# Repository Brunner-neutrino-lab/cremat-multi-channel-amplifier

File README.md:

# Multi-channel Cremat amplifier

A **12-channel** SiPM charge-sensitive preamplifier + Gaussian shaper board, derived
from the Brunner-lab **6-channel Cremat CSP & Shaper board**
([`cremat-x6-board`](reference/cremat-x6-board/)) with four deliberate changes:

1. **12 channels** (was 6).
2. **0805 passives wherever possible** (was a mix of larger imperial sizes).
3. **A Cremat CR-210 baseline restorer on every channel**, *optional* — populate the
   module **or** an 0805 `0R` jumper to bypass it.
4. **An on-board SiPM bias front-end on every channel**: a `BIAS_IN` feed through an
   *optional* RC-in-series-with-R **bias filter**, then a node shared by the **SiPM**
   (DC-coupled) and the **amplifier** (AC-coupled). The detector and the amplifier hang
   off the same biased node.

> This repository is the **design specification + build documentation** for the new
> board. It is structured to mirror the Brunner-lab **`ets-breakout`** project, which is
> included as the *reference for how to document and build*. The KiCad implementation is
> the next track (see [Status](#status)).

## What each channel does (new signal chain)

```
                          bias filter (optional, 0R-bypassable)
 BIAS_IN ───►  Rf1 ──┬── Rf2 ──►──┐
                     │            │   FRONT-END NODE
                    Cf            ├─────────────► SIPM   (DC-coupled: reverse-biases the detector)
                     │            │
                    GND           └─► Cc ─► CR-11X ─► CR-200-X ─► [CR-210] ─► buffer ─► OUTPUT
                                     (AC)   CSP        shaper     BLR(opt)   THS3491    (50 Ω
                                                       +P/Z trim  0R-byp.    DNP-def     coax)
```

- **`BIAS_IN` → bias filter → front-end node.** "RC in series with R": series `Rf1`,
  shunt `Cf` to ground, series `Rf2`. The whole filter is bypassable with 0R jumpers.
- **Front-end node → `SIPM` (DC-coupled).** The filtered bias voltage reverse-biases the
  detector directly.
- **Front-end node → `Cc` → amplifier (AC-coupled).** Only the SiPM's fast current pulse
  reaches the charge-sensitive preamp; the DC bias is blocked by `Cc`.
- **CR-11X → CR-200-X → CR-210 → buffer → output**, the classic Cremat chain. The CR-210
  baseline restorer is new and optional.

Full detail: [docs/hardware/channel.md](docs/hardware/channel.md).

## Documentation map

> **Looking for the actual orderable board? It is [`final-board/twelve-channel/`](final-board/twelve-channel/).**
> Reviewing it → [REVIEW.md](final-board/twelve-channel/REVIEW.md) · ordering it →
> [ORDERING.md](final-board/twelve-channel/ORDERING.md) · resuming work on it →
> [HANDOFF.md](final-board/twelve-channel/HANDOFF.md).

| Doc | Contents |
|-----|----------|
| **[final-board/twelve-channel/REVIEW.md](final-board/twelve-channel/REVIEW.md)** | **Design-review pack** — verified state, the acceptance gate, and what needs human eyes before ordering |
| [final-board/twelve-channel/INTERFACE.md](final-board/twelve-channel/INTERFACE.md) | The final board: layout intent, connector map, stackup, per-channel cell |
| [final-board/twelve-channel/ORDERING.md](final-board/twelve-channel/ORDERING.md) | Buy sheet — JLCPCB (fab + SMT) + DigiKey (hand parts), quantities, upload steps |
| [final-board/twelve-channel/HANDOFF.md](final-board/twelve-channel/HANDOFF.md) | Resume on a new machine: toolchain, paths, regeneration commands, gotchas |
| [docs/agent-project/](docs/agent-project/) | **Parallel agent-developed build** — bottom-up (per-chip eval boards → single channel → 12-ch board), 12 tracks with briefs, conventions, session-log/report protocol. **Start at [docs/agent-project/README.md](docs/agent-project/README.md).** *(Historical: intermediate figures here — e.g. bias ≤ 60 V, board 235.1 × 264.1 mm — are superseded by the final board.)* |
| [docs/development-plan.md](docs/development-plan.md) | Earlier work-track breakdown (the rapid top-down build in `hardware/`); superseded by the agent-project for the final design |
| [docs/architecture.md](docs/architecture.md) | System/board block diagram, channel signal chain, design partitioning |
| [docs/modifications.md](docs/modifications.md) | **The four changes vs. `cremat-x6-board`, with rationale + the optional/DNP jumper scheme** |
| [docs/hardware/channel.md](docs/hardware/channel.md) | Per-channel circuit: bias front-end, AC/DC coupling, CSP/shaper/BLR/buffer, jumpers |
| [docs/hardware/circuit-design.md](docs/hardware/circuit-design.md) | **Front-end values for the Hamamatsu VUV4** — bias filter, coupling, polarity, CR-112 gain/range |
| [docs/hardware/board.md](docs/hardware/board.md) | 12-channel board: power distribution, connectors, layout intent |
| [docs/hardware/bom.md](docs/hardware/bom.md) | 0805 strategy, Cremat modules, optional-population (DNP) variants |
| [docs/hardware/pcb-design-rules.md](docs/hardware/pcb-design-rules.md) | Net classes, trace widths, HV creepage, guard rings |
| [docs/hardware/component-libraries.md](docs/hardware/component-libraries.md) | Symbols + footprints to provide (Cremat SIP-8, 0805 passives, jumpers) |
| [docs/fabrication/fabrication-guide.md](docs/fabrication/fabrication-guide.md) | Fab output generation, assembly, population variants |
| [docs/operation/user-guide.md](docs/operation/user-guide.md) | Power-up, biasing SiPMs, choosing populate/bypass options |
| [docs/session-report.md](docs/session-report.md) | Integration/manager handoff: tracks, decisions, what's done vs. open |

## References (git submodules)

| Path | Repo | Role |
|------|------|------|
| [reference/cremat-x6-board/](reference/cremat-x6-board/) | `Brunner-neutrino-lab/cremat-x6-board` | **What we're building** — the 6-channel CR-110/CR-200 eval board this design derives from |
| [reference/ets-breakout/](reference/ets-breakout/) | `Brunner-neutrino-lab/ets-breakout` | **How we build/document** — KiCad-from-source-of-truth pipeline + doc structure to imitate |
| [reference/cremat-CR-160-R7/](reference/cremat-CR-160-R7/) | `CrematInc/CR-160-R7` | **CR-210 pinout + integration** — Cremat's open-source CR-200/CR-210 eval board (the CR-210 bypass-jumper scheme) |
| [reference/cremat-CR-150-R5/](reference/cremat-CR-150-R5/) | `CrematInc/CR-150-R5` | **CR-11X reference** — Cremat's open-source CSP eval board (source of the CR-11X symbol) |

Clone with submodules:

```
git clone --recurse-submodules <this-repo>
# or, in an existing clone:
git submodule update --init --recursive
```

## Status

- **Specification + documentation: complete.** This repo fully specifies the modified
  12-channel board.
- **Development is divided into tracks** — see [docs/development-plan.md](docs/development-plan.md).
  **Phase 1 is built:** [hardware/](hardware/) has the `kicad-cli`-validated symbol library
  ([hardware/lib/cremat.kicad_sym](hardware/lib/cremat.kicad_sym)), the project + net classes,
  lib tables, the fielded BOM ([hardware/bom/](hardware/bom/)), the golden per-channel netlist
  ([hardware/integration-notes.md](hardware/integration-notes.md)), and the mechanical spec
  ([hardware/mechanical.md](hardware/mechanical.md)). **Track 5 (schematic) is done** — the
  12-channel hierarchical schematic is generated by [hardware/gen_sch.py](hardware/gen_sch.py)
  and is **ERC-clean (0 errors)** with a netlist that matches the spec node-by-node. **Layout
  + fab (Tracks 6–7)** remain — guide: [hardware/BUILD-IN-KICAD.md](hardware/BUILD-IN-KICAD.md).
- **CR-210 pinout + bypass-jumper integration: confirmed** against Cremat's open-source
  [CR-160-R7](reference/cremat-CR-160-R7/) board (pin 2 = GND vs the CR-200's P/Z).
- **Build decisions resolved** (D1–D6, see the plan): bias ≤ 70 V (100 V parts); all
  per-channel I/O is **MCX `CONMCX013`** (`BIAS_IN`, `SIPM`, `TEST`, `OUT_50` — **`BIAS_IN` is
  per-channel**, 4/channel → 48 MCX/board); modules **CR-112** + **CR-200-1µs** (+ CR-210),
  **socketed** on Samtec SS-108-TT-2 SIP-8 sockets (36/board), the modules plug in; rack-mounted,
  **one board per 1U Hammond RM1U1908VBK case, boards daisy-chained**; first build = Full.
- **Front-end designed for the Hamamatsu VUV4** (S13370, 45–55 V, ≈220 fC/V, Cdet≈1.28 nF):
  bias filter `Rf1=Rf2=10 kΩ`, `Cf=100 nF`, `Cc=0.22 µF`; cathode-on-node +45–55 V; CR-112
  ([docs/hardware/circuit-design.md](docs/hardware/circuit-design.md)).
- **Enclosure (D5):** **Hammond RM1U1908VBK** (1U, vented), **one board per case**; boards are
  **daisy-chained** (each board in its own 1U box, `J_DAISY` passes the raw rails box-to-box).
  Board outline **213.2 × 334.7 mm**; it mounts on standoffs off the bottom cover and passes
  **through a ~340 × 7 mm milled slot** in each front/rear panel (slot-through, protruding ~5 mm;
  the MCX faces sit ~8.6 mm proud). Usable interior height 40.09 mm; tall parts must clear it.
  Inputs (`BIAS_IN`+`SIPM`) on one long edge, outputs (`OUT_50`) on the other (24 MCX per long edge).
- **Open items**: final jack/outline placement (Track 4), and bench-verify (CR-112 output
  sign, warm/cold OV offset, single-p.e. range, P/Z trim). Power terminals are resolved —
  two 3-pos 5.08 mm Phoenix screw terminals, `J_PWR` (supply in) + `J_DAISY` (raw rails out).

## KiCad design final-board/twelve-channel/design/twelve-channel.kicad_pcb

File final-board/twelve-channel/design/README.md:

# twelve-channel — design (schematic + PCB)

12-channel SiPM CSP + shaper + BLR + buffer board, built from the reworked single channel
(`../../../integration/single-channel/design/`) as the single source of truth.

- **Schematic** = KiCad **hierarchical**: the single channel (minus board power entry)
  instantiated 12× as `channel.kicad_sch`, plus a root `twelve-channel.kicad_sch` with the 12
  sheet instances + one common power section (power in + board-to-board daisy + up-rated
  reverse-polarity/PTC block + 470 µF bulk). Per-channel nets auto-scope to `/chNN/<net>`.
- **PCB** = **tile-and-replicate**: the routed single-channel channel row is cloned 12× (offset
  25 mm in Y, refs re-mapped via role, nets re-mapped `/X`→`/chNN/X`); board-wide plane pours
  carry the rails so the router does no per-channel work; only the common section is routed.

## Pipeline (run in order; KiCad 10 bundled Python)

```
PY="C:/Program Files/KiCad/10.0/bin/python.exe"
CLI="C:/Program Files/KiCad/10.0/bin/kicad-cli.exe"

# --- schematic ---
"$PY" gen_sch.py                       # -> channel.kicad_sch, twelve-channel.kicad_sch, .kicad_pro
"$CLI" sch erc twelve-channel.kicad_sch
"$CLI" sch export netlist --format kicadsexpr -o twelve-channel.net twelve-channel.kicad_sch

# --- PCB (needs twelve-channel.net from the step above) ---
"$PY" gen_pcb.py                       # tile x12 + common section + planes + outline (+ .kicad_dru)
"$PY" fill_zones.py                    # fill the 4 plane zones (separate pass; in-memory fill segfaults)
"$PY" polish_silk.py                   # move dense refdes/fields F.Silkscreen -> F.Fab
"$CLI" pcb drc --schematic-parity twelve-channel.kicad_pcb    # gate: 0 / 0 / 0
```

Note: `gen_pcb.py` resets silk and adds visible common-part fields, so **`polish_silk.py` must
run after every `gen_pcb.py`**. The `twelve-channel.net` netlist is the authoritative source
for the PCB's per-pad nets, footprint values, and BOM fields (regenerate it after any schematic
change before re-running `gen_pcb.py`).

## Result

213.2 × 334.7 mm, 4-layer (widened 138 → 180 → 213.2 mm to span the Hammond RM1U1908VBK 1U case —
one board per case, slot-through the front/rear panels; the output/bias MCX row was shifted to the
far edge with F.Cu trace extensions). 468 footprints (464 refdes'd parts + 4 M3), 4 plane
zones. (The BOM lists 500 line-item parts = the 464 placed + the 36 SIP-8 sockets, which
share the module sites' PinSocket_1x08 footprints.)
**DRC 0 violations / 0 unconnected / 0 schematic-parity.** Render: `twelve-channel-3d.png`.

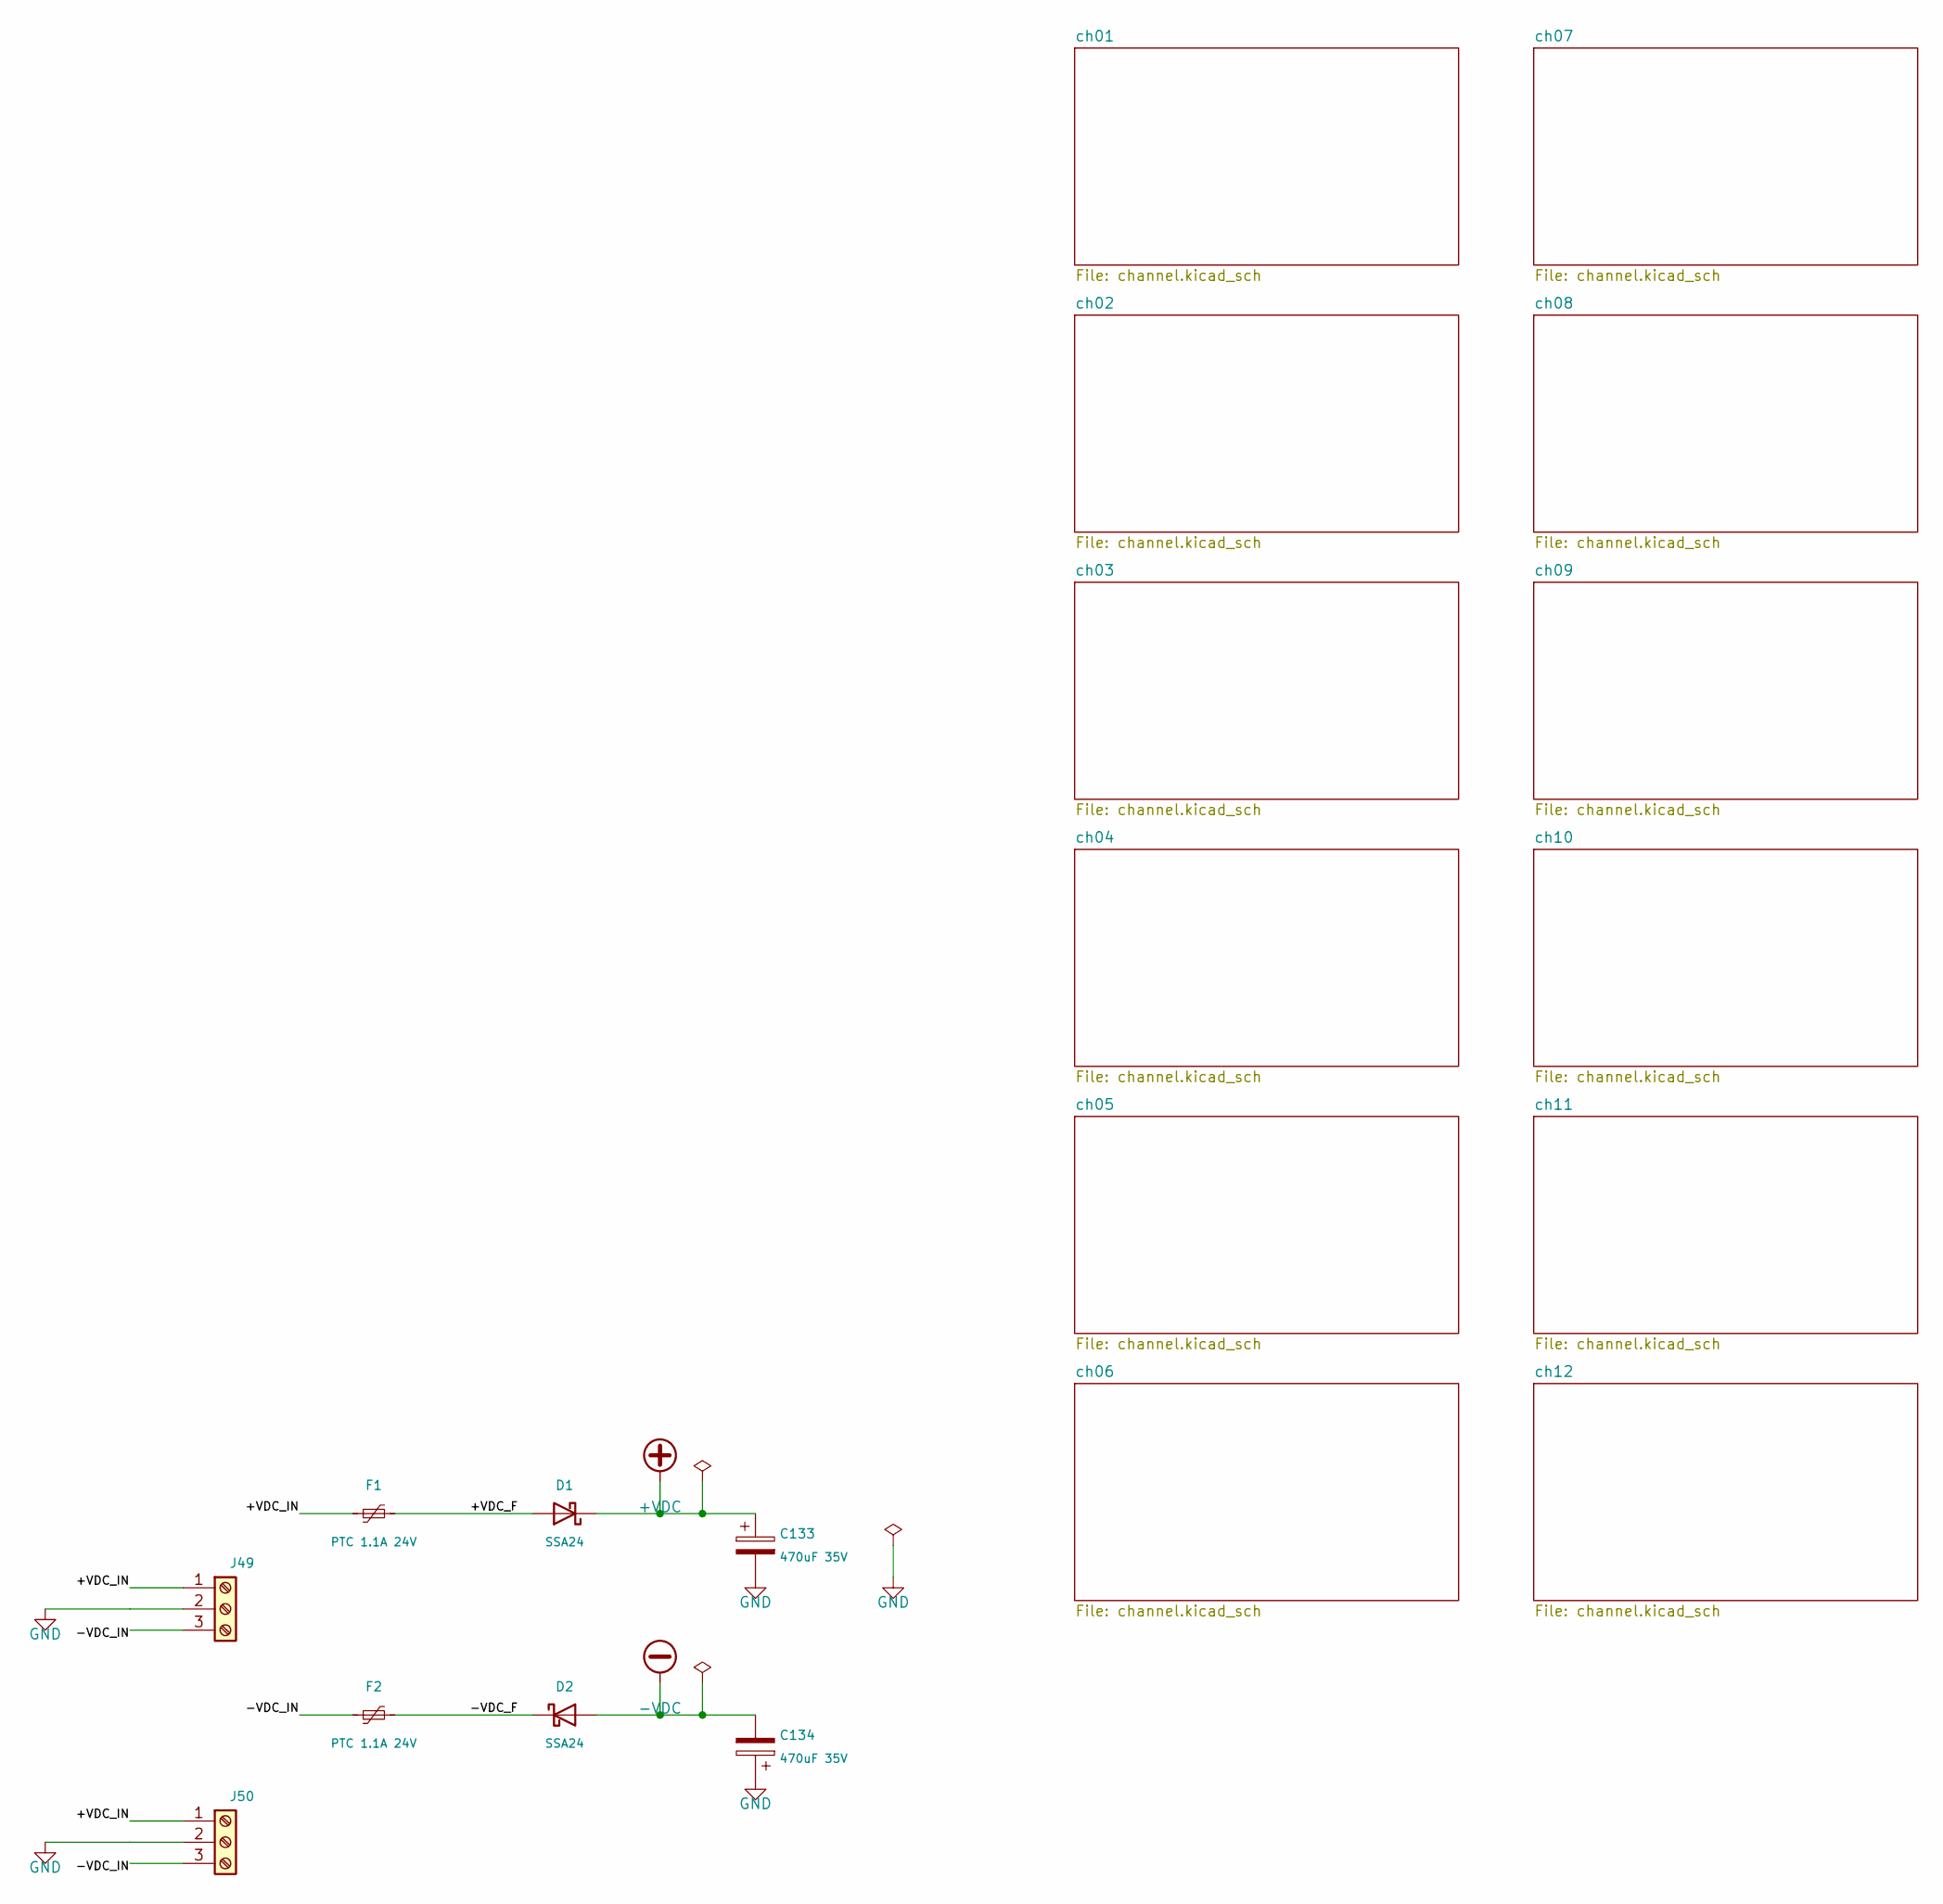
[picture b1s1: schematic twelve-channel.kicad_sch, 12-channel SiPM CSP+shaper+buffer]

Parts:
C133, C134: 470uF 35V; CP_Elec_10x10.5; MPN EEE-FN1V471UP
D1, D2: SSA24; D_SMA; MPN SSA24
F1, F2: PTC 1.1A 24V; Fuse_1812_4532Metric; MPN 1812L110/24DR
J49, J50: Screw terminal 3-pos 5.08mm; TerminalBlock_Phoenix_MKDS-1,5-3_1x03_P5.00mm_Horizontal; MPN 1715734

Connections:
+VDC: C133.1, D1.1 (K); also elsewhere on the board
-VDC: C134.2, D2.2 (A); also elsewhere on the board
/+VDC_F: D1.2 (A), F1.2
/+VDC_IN: F1.1, J49.1, J50.1
/-VDC_F: D2.1 (K), F2.2
/-VDC_IN: F2.1, J49.3, J50.3
GND: C133.2, C134.1, J49.2, J50.2; also elsewhere on the board

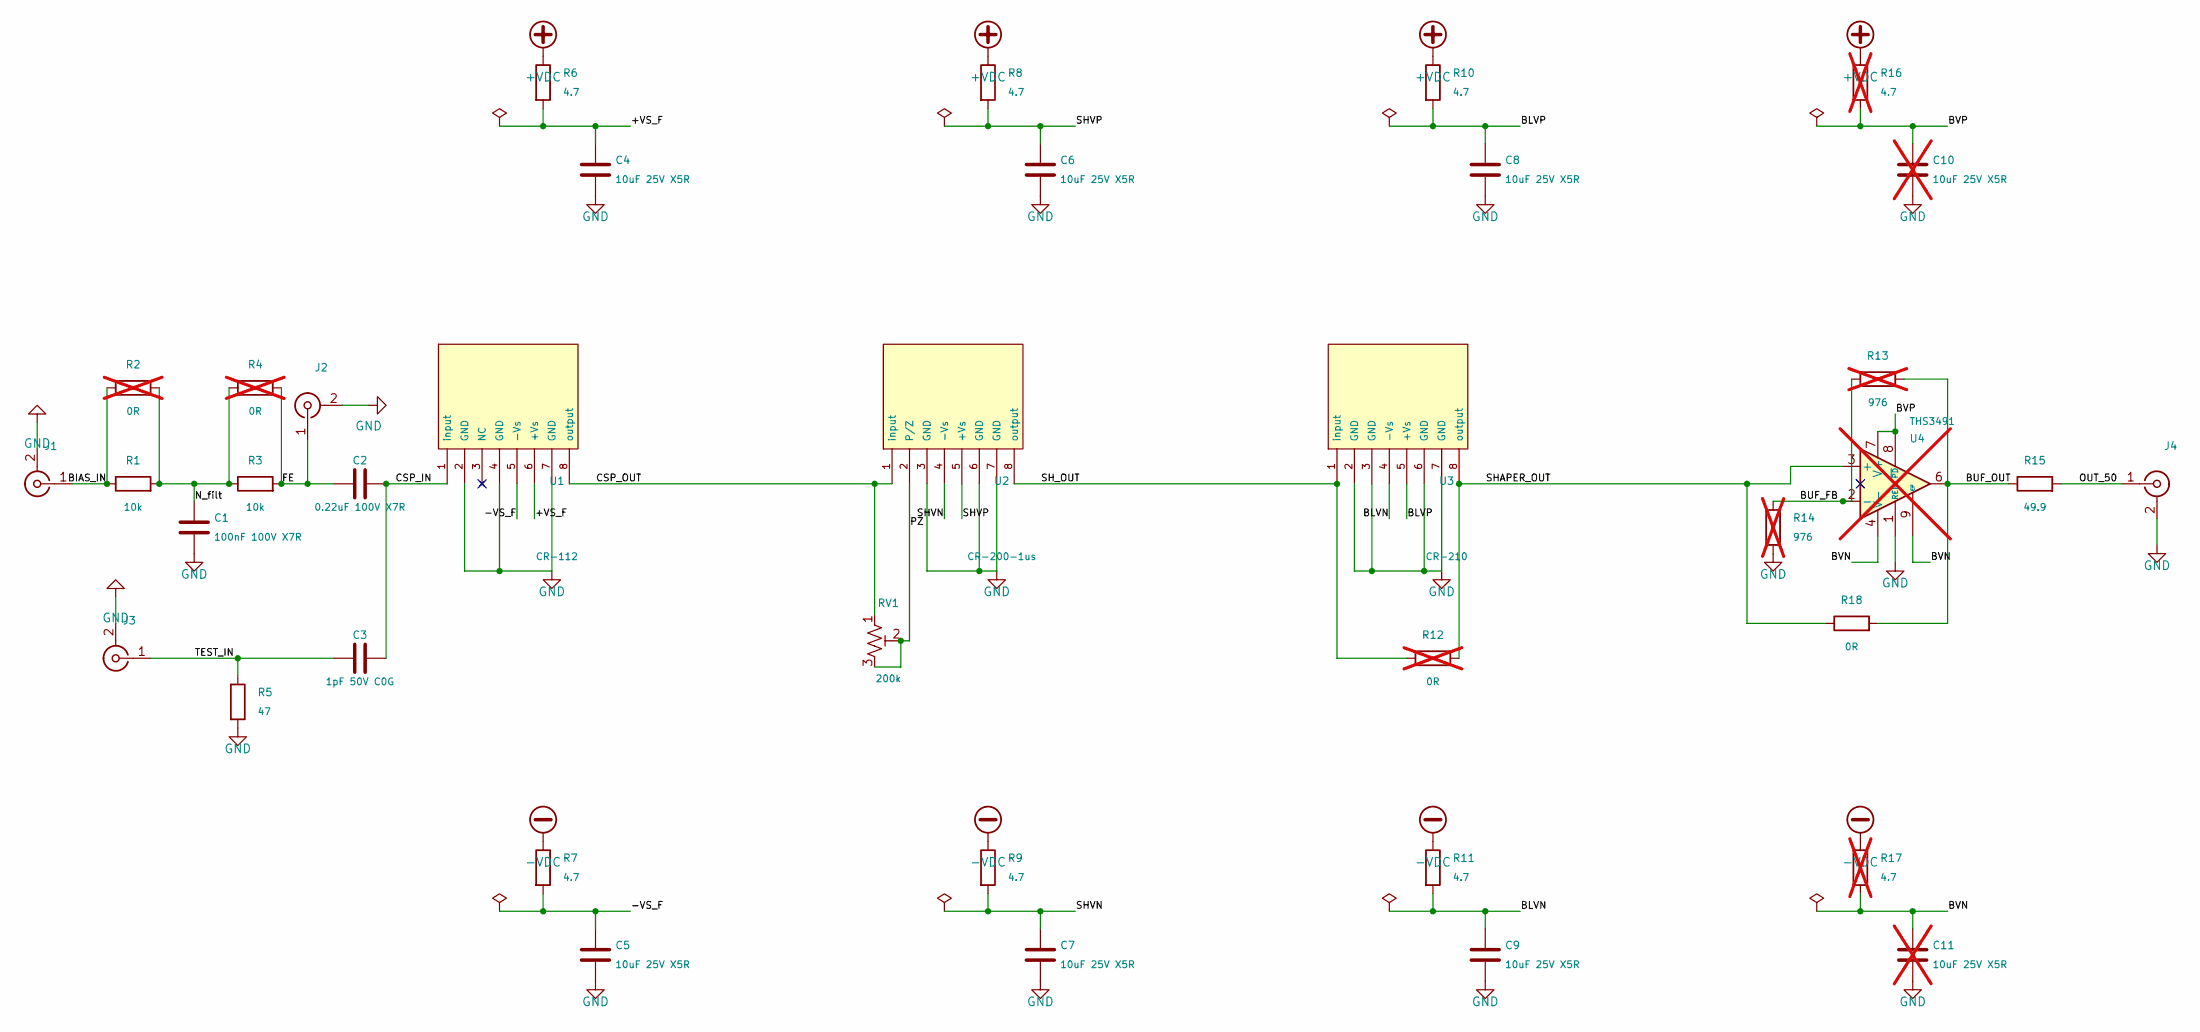
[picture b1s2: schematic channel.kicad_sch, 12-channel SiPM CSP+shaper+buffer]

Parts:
C1: 100nF 100V X7R; C_0805_2012Metric; MPN CL21B104KCFNNNE
C2: 0.22uF 100V X7R; C_0805_2012Metric; MPN C0805C224K1RACTU
C3: 1pF 50V C0G; C_0805_2012Metric; MPN CC0805CRNPO9BN1R0
C4, C5, C6, C7, C8, C9: 10uF 25V X5R; C_0805_2012Metric; MPN C0805C106K3PACTU
C10, C11: 10uF 25V X5R; C_0805_2012Metric; MPN C0805C106K3PACTU; not fitted
J1, J2, J3, J4: MCX edge jack 50R; MCX_CONMCX013-T; MPN CONMCX013
R1, R3: 10k; R_0805_2012Metric; MPN RC0805FR-0710KL
R2, R4, R12: 0R; R_0805_2012Metric; MPN RC0805JR-070RL; not fitted
R5: 47; R_0805_2012Metric; MPN RC0805JR-0747RL
R6, R7, R8, R9, R10, R11: 4.7; R_0805_2012Metric; MPN RC0805JR-074R7L
R13, R14: 976; R_0805_2012Metric; MPN RC0805FR-07976RL; not fitted
R15: 49.9; R_0805_2012Metric; MPN RC0805FR-0749R9L
R16, R17: 4.7; R_0805_2012Metric; MPN RC0805JR-074R7L; not fitted
R18: 0R; R_0805_2012Metric; MPN RC0805JR-070RL
RV1: 200k; Potentiometer_Bourns_3296W_Vertical; MPN 3296W-1-204LF
U1: CR-112; PinSocket_1x08_P2.54mm_Vertical; MPN CR-112-R2.1
U2: CR-200-1us; PinSocket_1x08_P2.54mm_Vertical; MPN CR-200-1us-R2.1
U3: CR-210; PinSocket_1x08_P2.54mm_Vertical; MPN CR-210-R0
U4: THS3491; SOIC-8-1EP_3.9x4.9mm_P1.27mm_EP2.29x3mm; MPN THS3491IDDAT; not fitted

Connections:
+VDC: R6.1, R8.1, R10.1, R16.1; also elsewhere on the board
-VDC: R7.1, R9.1, R11.1, R17.1; also elsewhere on the board
/ch01/+VS_F: C4.1, R6.2, U1.6 (+Vs)
/ch01/-VS_F: C5.1, R7.2, U1.5 (-Vs)
/ch01/BIAS_IN: J1.1 (In), R1.1, R2.1
/ch01/BLVN: C9.1, R11.2, U3.4 (-Vs)
/ch01/BLVP: C8.1, R10.2, U3.5 (+Vs)
/ch01/BUF_FB: R13.2, R14.1, U4.2 (-)
/ch01/BUF_OUT: R13.1, R15.1, R18.2, U4.6
/ch01/BVN: C11.1, R17.2, U4.4 (V-), U4.9 (EP)
/ch01/BVP: C10.1, R16.2, U4.7 (V+), U4.8 (~PD)
/ch01/CSP_IN: C2.2, C3.2, U1.1 (input)
/ch01/CSP_OUT: RV1.1, U1.8 (output), U2.1 (input)
/ch01/FE: C2.1, J2.1 (In), R3.2, R4.2
/ch01/N_filt: C1.1, R1.2, R2.2, R3.1, R4.1
/ch01/OUT_50: J4.1 (In), R15.2
/ch01/PZ: RV1.2, RV1.3, U2.2 (P/Z)
/ch01/SHAPER_OUT: R12.2, R18.1, U3.8 (output), U4.3 (+)
/ch01/SHVN: C7.1, R9.2, U2.4 (-Vs)
/ch01/SHVP: C6.1, R8.2, U2.5 (+Vs)
/ch01/SH_OUT: R12.1, U2.8 (output), U3.1 (input)
/ch01/TEST_IN: C3.1, J3.1 (In), R5.1
GND: C1.2, C4.2, C5.2, C6.2, C7.2, C8.2, C9.2, C10.2, C11.2, J1.2 (Ext), J2.2 (Ext), J3.2 (Ext), J4.2 (Ext), R5.2, R14.2, U1.2 (GND), U1.4 (GND), U1.7 (GND), U2.3 (GND), U2.6 (GND), U2.7 (GND), U3.2 (GND), U3.3 (GND), U3.6 (GND), U3.7 (GND), U4.1 (REF); also elsewhere on the board

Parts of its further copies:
C12, C23, C34, C45, C56, C67, C78, C89, C100, C111, C122: 100nF 100V X7R; C_0805_2012Metric; MPN CL21B104KCFNNNE
C13, C24, C35, C46, C57, C68, C79, C90, C101, C112, C123: 0.22uF 100V X7R; C_0805_2012Metric; MPN C0805C224K1RACTU
C14, C25, C36, C47, C58, C69, C80, C91, C102, C113, C124: 1pF 50V C0G; C_0805_2012Metric; MPN CC0805CRNPO9BN1R0
C15, C16, C17, C18, C19, C20, C26, C27, C28, C29, C30, C31, C37, C38, C39, C40, C41, C42, C48, C49, C50, C51, C52, C53, C59, C60, C61, C62, C63, C64, C70, C71, C72, C73, C74, C75, C81, C82, C83, C84, C85, C86, C92, C93, C94, C95, C96, C97, C103, C104, C105, C106, C107, C108, C114, C115, C116, C117, C118, C119, C125, C126, C127, C128, C129, C130: 10uF 25V X5R; C_0805_2012Metric; MPN C0805C106K3PACTU
C21, C22, C32, C33, C43, C44, C54, C55, C65, C66, C76, C77, C87, C88, C98, C99, C109, C110, C120, C121, C131, C132: 10uF 25V X5R; C_0805_2012Metric; MPN C0805C106K3PACTU; not fitted
J5, J6, J7, J8, J9, J10, J11, J12, J13, J14, J15, J16, J17, J18, J19, J20, J21, J22, J23, J24, J25, J26, J27, J28, J29, J30, J31, J32, J33, J34, J35, J36, J37, J38, J39, J40, J41, J42, J43, J44, J45, J46, J47, J48: MCX edge jack 50R; MCX_CONMCX013-T; MPN CONMCX013
R19, R21, R37, R39, R55, R57, R73, R75, R91, R93, R109, R111, R127, R129, R145, R147, R163, R165, R181, R183, R199, R201: 10k; R_0805_2012Metric; MPN RC0805FR-0710KL
R20, R22, R30, R38, R40, R48, R56, R58, R66, R74, R76, R84, R92, R94, R102, R110, R112, R120, R128, R130, R138, R146, R148, R156, R164, R166, R174, R182, R184, R192, R200, R202, R210: 0R; R_0805_2012Metric; MPN RC0805JR-070RL; not fitted
R23, R41, R59, R77, R95, R113, R131, R149, R167, R185, R203: 47; R_0805_2012Metric; MPN RC0805JR-0747RL
R24, R25, R26, R27, R28, R29, R42, R43, R44, R45, R46, R47, R60, R61, R62, R63, R64, R65, R78, R79, R80, R81, R82, R83, R96, R97, R98, R99, R100, R101, R114, R115, R116, R117, R118, R119, R132, R133, R134, R135, R136, R137, R150, R151, R152, R153, R154, R155, R168, R169, R170, R171, R172, R173, R186, R187, R188, R189, R190, R191, R204, R205, R206, R207, R208, R209: 4.7; R_0805_2012Metric; MPN RC0805JR-074R7L
R31, R32, R49, R50, R67, R68, R85, R86, R103, R104, R121, R122, R139, R140, R157, R158, R175, R176, R193, R194, R211, R212: 976; R_0805_2012Metric; MPN RC0805FR-07976RL; not fitted
R33, R51, R69, R87, R105, R123, R141, R159, R177, R195, R213: 49.9; R_0805_2012Metric; MPN RC0805FR-0749R9L
R34, R35, R52, R53, R70, R71, R88, R89, R106, R107, R124, R125, R142, R143, R160, R161, R178, R179, R196, R197, R214, R215: 4.7; R_0805_2012Metric; MPN RC0805JR-074R7L; not fitted
R36, R54, R72, R90, R108, R126, R144, R162, R180, R198, R216: 0R; R_0805_2012Metric; MPN RC0805JR-070RL
RV2, RV3, RV4, RV5, RV6, RV7, RV8, RV9, RV10, RV11, RV12: 200k; Potentiometer_Bourns_3296W_Vertical; MPN 3296W-1-204LF
U5, U9, U13, U17, U21, U25, U29, U33, U37, U41, U45: CR-112; PinSocket_1x08_P2.54mm_Vertical; MPN CR-112-R2.1
U6, U10, U14, U18, U22, U26, U30, U34, U38, U42, U46: CR-200-1us; PinSocket_1x08_P2.54mm_Vertical; MPN CR-200-1us-R2.1
U7, U11, U15, U19, U23, U27, U31, U35, U39, U43, U47: CR-210; PinSocket_1x08_P2.54mm_Vertical; MPN CR-210-R0
U8, U12, U16, U20, U24, U28, U32, U36, U40, U44, U48: THS3491; SOIC-8-1EP_3.9x4.9mm_P1.27mm_EP2.29x3mm; MPN THS3491IDDAT; not fitted

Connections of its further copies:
+VDC: R24.1, R26.1, R28.1, R34.1, R42.1, R44.1, R46.1, R52.1, R60.1, R62.1, R64.1, R70.1, R78.1, R80.1, R82.1, R88.1, R96.1, R98.1, R100.1, R106.1, R114.1, R116.1, R118.1, R124.1, R132.1, R134.1, R136.1, R142.1, R150.1, R152.1, R154.1, R160.1, R168.1, R170.1, R172.1, R178.1, R186.1, R188.1, R190.1, R196.1, R204.1, R206.1, R208.1, R214.1; also elsewhere on the board
-VDC: R25.1, R27.1, R29.1, R35.1, R43.1, R45.1, R47.1, R53.1, R61.1, R63.1, R65.1, R71.1, R79.1, R81.1, R83.1, R89.1, R97.1, R99.1, R101.1, R107.1, R115.1, R117.1, R119.1, R125.1, R133.1, R135.1, R137.1, R143.1, R151.1, R153.1, R155.1, R161.1, R169.1, R171.1, R173.1, R179.1, R187.1, R189.1, R191.1, R197.1, R205.1, R207.1, R209.1, R215.1; also elsewhere on the board
/ch02/+VS_F: C15.1, R24.2, U5.6 (+Vs)
/ch02/-VS_F: C16.1, R25.2, U5.5 (-Vs)
/ch02/BIAS_IN: J5.1 (In), R19.1, R20.1
/ch02/BLVN: C20.1, R29.2, U7.4 (-Vs)
/ch02/BLVP: C19.1, R28.2, U7.5 (+Vs)
/ch02/BUF_FB: R31.2, R32.1, U8.2 (-)
/ch02/BUF_OUT: R31.1, R33.1, R36.2, U8.6
/ch02/BVN: C22.1, R35.2, U8.4 (V-), U8.9 (EP)
/ch02/BVP: C21.1, R34.2, U8.7 (V+), U8.8 (~PD)
/ch02/CSP_IN: C13.2, C14.2, U5.1 (input)
/ch02/CSP_OUT: RV2.1, U5.8 (output), U6.1 (input)
/ch02/FE: C13.1, J6.1 (In), R21.2, R22.2
/ch02/N_filt: C12.1, R19.2, R20.2, R21.1, R22.1
/ch02/OUT_50: J8.1 (In), R33.2
/ch02/PZ: RV2.2, RV2.3, U6.2 (P/Z)
/ch02/SHAPER_OUT: R30.2, R36.1, U7.8 (output), U8.3 (+)
/ch02/SHVN: C18.1, R27.2, U6.4 (-Vs)
/ch02/SHVP: C17.1, R26.2, U6.5 (+Vs)
/ch02/SH_OUT: R30.1, U6.8 (output), U7.1 (input)
/ch02/TEST_IN: C14.1, J7.1 (In), R23.1
/ch03/+VS_F: C26.1, R42.2, U9.6 (+Vs)
/ch03/-VS_F: C27.1, R43.2, U9.5 (-Vs)
/ch03/BIAS_IN: J9.1 (In), R37.1, R38.1
/ch03/BLVN: C31.1, R47.2, U11.4 (-Vs)
/ch03/BLVP: C30.1, R46.2, U11.5 (+Vs)
/ch03/BUF_FB: R49.2, R50.1, U12.2 (-)
/ch03/BUF_OUT: R49.1, R51.1, R54.2, U12.6
/ch03/BVN: C33.1, R53.2, U12.4 (V-), U12.9 (EP)
/ch03/BVP: C32.1, R52.2, U12.7 (V+), U12.8 (~PD)
/ch03/CSP_IN: C24.2, C25.2, U9.1 (input)
/ch03/CSP_OUT: RV3.1, U9.8 (output), U10.1 (input)
/ch03/FE: C24.1, J10.1 (In), R39.2, R40.2
/ch03/N_filt: C23.1, R37.2, R38.2, R39.1, R40.1
/ch03/OUT_50: J12.1 (In), R51.2
/ch03/PZ: RV3.2, RV3.3, U10.2 (P/Z)
/ch03/SHAPER_OUT: R48.2, R54.1, U11.8 (output), U12.3 (+)
/ch03/SHVN: C29.1, R45.2, U10.4 (-Vs)
/ch03/SHVP: C28.1, R44.2, U10.5 (+Vs)
/ch03/SH_OUT: R48.1, U10.8 (output), U11.1 (input)
/ch03/TEST_IN: C25.1, J11.1 (In), R41.1
/ch04/+VS_F: C37.1, R60.2, U13.6 (+Vs)
/ch04/-VS_F: C38.1, R61.2, U13.5 (-Vs)
/ch04/BIAS_IN: J13.1 (In), R55.1, R56.1
/ch04/BLVN: C42.1, R65.2, U15.4 (-Vs)
/ch04/BLVP: C41.1, R64.2, U15.5 (+Vs)
/ch04/BUF_FB: R67.2, R68.1, U16.2 (-)
/ch04/BUF_OUT: R67.1, R69.1, R72.2, U16.6
/ch04/BVN: C44.1, R71.2, U16.4 (V-), U16.9 (EP)
/ch04/BVP: C43.1, R70.2, U16.7 (V+), U16.8 (~PD)
/ch04/CSP_IN: C35.2, C36.2, U13.1 (input)
/ch04/CSP_OUT: RV4.1, U13.8 (output), U14.1 (input)
/ch04/FE: C35.1, J14.1 (In), R57.2, R58.2
/ch04/N_filt: C34.1, R55.2, R56.2, R57.1, R58.1
/ch04/OUT_50: J16.1 (In), R69.2
/ch04/PZ: RV4.2, RV4.3, U14.2 (P/Z)
/ch04/SHAPER_OUT: R66.2, R72.1, U15.8 (output), U16.3 (+)
/ch04/SHVN: C40.1, R63.2, U14.4 (-Vs)
/ch04/SHVP: C39.1, R62.2, U14.5 (+Vs)
/ch04/SH_OUT: R66.1, U14.8 (output), U15.1 (input)
/ch04/TEST_IN: C36.1, J15.1 (In), R59.1
/ch05/+VS_F: C48.1, R78.2, U17.6 (+Vs)
/ch05/-VS_F: C49.1, R79.2, U17.5 (-Vs)
/ch05/BIAS_IN: J17.1 (In), R73.1, R74.1
/ch05/BLVN: C53.1, R83.2, U19.4 (-Vs)
/ch05/BLVP: C52.1, R82.2, U19.5 (+Vs)
/ch05/BUF_FB: R85.2, R86.1, U20.2 (-)
/ch05/BUF_OUT: R85.1, R87.1, R90.2, U20.6
/ch05/BVN: C55.1, R89.2, U20.4 (V-), U20.9 (EP)
/ch05/BVP: C54.1, R88.2, U20.7 (V+), U20.8 (~PD)
/ch05/CSP_IN: C46.2, C47.2, U17.1 (input)
/ch05/CSP_OUT: RV5.1, U17.8 (output), U18.1 (input)
/ch05/FE: C46.1, J18.1 (In), R75.2, R76.2
/ch05/N_filt: C45.1, R73.2, R74.2, R75.1, R76.1
/ch05/OUT_50: J20.1 (In), R87.2
/ch05/PZ: RV5.2, RV5.3, U18.2 (P/Z)
/ch05/SHAPER_OUT: R84.2, R90.1, U19.8 (output), U20.3 (+)
/ch05/SHVN: C51.1, R81.2, U18.4 (-Vs)
/ch05/SHVP: C50.1, R80.2, U18.5 (+Vs)
/ch05/SH_OUT: R84.1, U18.8 (output), U19.1 (input)
/ch05/TEST_IN: C47.1, J19.1 (In), R77.1
/ch06/+VS_F: C59.1, R96.2, U21.6 (+Vs)
/ch06/-VS_F: C60.1, R97.2, U21.5 (-Vs)
/ch06/BIAS_IN: J21.1 (In), R91.1, R92.1
/ch06/BLVN: C64.1, R101.2, U23.4 (-Vs)
/ch06/BLVP: C63.1, R100.2, U23.5 (+Vs)
/ch06/BUF_FB: R103.2, R104.1, U24.2 (-)
/ch06/BUF_OUT: R103.1, R105.1, R108.2, U24.6
/ch06/BVN: C66.1, R107.2, U24.4 (V-), U24.9 (EP)
/ch06/BVP: C65.1, R106.2, U24.7 (V+), U24.8 (~PD)
/ch06/CSP_IN: C57.2, C58.2, U21.1 (input)
/ch06/CSP_OUT: RV6.1, U21.8 (output), U22.1 (input)
/ch06/FE: C57.1, J22.1 (In), R93.2, R94.2
/ch06/N_filt: C56.1, R91.2, R92.2, R93.1, R94.1
/ch06/OUT_50: J24.1 (In), R105.2
/ch06/PZ: RV6.2, RV6.3, U22.2 (P/Z)
/ch06/SHAPER_OUT: R102.2, R108.1, U23.8 (output), U24.3 (+)
/ch06/SHVN: C62.1, R99.2, U22.4 (-Vs)
/ch06/SHVP: C61.1, R98.2, U22.5 (+Vs)
/ch06/SH_OUT: R102.1, U22.8 (output), U23.1 (input)
/ch06/TEST_IN: C58.1, J23.1 (In), R95.1
/ch07/+VS_F: C70.1, R114.2, U25.6 (+Vs)
/ch07/-VS_F: C71.1, R115.2, U25.5 (-Vs)
/ch07/BIAS_IN: J25.1 (In), R109.1, R110.1
/ch07/BLVN: C75.1, R119.2, U27.4 (-Vs)
/ch07/BLVP: C74.1, R118.2, U27.5 (+Vs)
/ch07/BUF_FB: R121.2, R122.1, U28.2 (-)
/ch07/BUF_OUT: R121.1, R123.1, R126.2, U28.6
/ch07/BVN: C77.1, R125.2, U28.4 (V-), U28.9 (EP)
/ch07/BVP: C76.1, R124.2, U28.7 (V+), U28.8 (~PD)
/ch07/CSP_IN: C68.2, C69.2, U25.1 (input)
/ch07/CSP_OUT: RV7.1, U25.8 (output), U26.1 (input)
/ch07/FE: C68.1, J26.1 (In), R111.2, R112.2
/ch07/N_filt: C67.1, R109.2, R110.2, R111.1, R112.1
/ch07/OUT_50: J28.1 (In), R123.2
/ch07/PZ: RV7.2, RV7.3, U26.2 (P/Z)
/ch07/SHAPER_OUT: R120.2, R126.1, U27.8 (output), U28.3 (+)
/ch07/SHVN: C73.1, R117.2, U26.4 (-Vs)
/ch07/SHVP: C72.1, R116.2, U26.5 (+Vs)
/ch07/SH_OUT: R120.1, U26.8 (output), U27.1 (input)
/ch07/TEST_IN: C69.1, J27.1 (In), R113.1
/ch08/+VS_F: C81.1, R132.2, U29.6 (+Vs)
/ch08/-VS_F: C82.1, R133.2, U29.5 (-Vs)
/ch08/BIAS_IN: J29.1 (In), R127.1, R128.1
/ch08/BLVN: C86.1, R137.2, U31.4 (-Vs)
/ch08/BLVP: C85.1, R136.2, U31.5 (+Vs)
/ch08/BUF_FB: R139.2, R140.1, U32.2 (-)
/ch08/BUF_OUT: R139.1, R141.1, R144.2, U32.6
/ch08/BVN: C88.1, R143.2, U32.4 (V-), U32.9 (EP)
/ch08/BVP: C87.1, R142.2, U32.7 (V+), U32.8 (~PD)
/ch08/CSP_IN: C79.2, C80.2, U29.1 (input)
/ch08/CSP_OUT: RV8.1, U29.8 (output), U30.1 (input)
/ch08/FE: C79.1, J30.1 (In), R129.2, R130.2
/ch08/N_filt: C78.1, R127.2, R128.2, R129.1, R130.1
/ch08/OUT_50: J32.1 (In), R141.2
/ch08/PZ: RV8.2, RV8.3, U30.2 (P/Z)
/ch08/SHAPER_OUT: R138.2, R144.1, U31.8 (output), U32.3 (+)
/ch08/SHVN: C84.1, R135.2, U30.4 (-Vs)
/ch08/SHVP: C83.1, R134.2, U30.5 (+Vs)
/ch08/SH_OUT: R138.1, U30.8 (output), U31.1 (input)
/ch08/TEST_IN: C80.1, J31.1 (In), R131.1
/ch09/+VS_F: C92.1, R150.2, U33.6 (+Vs)
/ch09/-VS_F: C93.1, R151.2, U33.5 (-Vs)
/ch09/BIAS_IN: J33.1 (In), R145.1, R146.1
/ch09/BLVN: C97.1, R155.2, U35.4 (-Vs)
/ch09/BLVP: C96.1, R154.2, U35.5 (+Vs)
/ch09/BUF_FB: R157.2, R158.1, U36.2 (-)
/ch09/BUF_OUT: R157.1, R159.1, R162.2, U36.6
/ch09/BVN: C99.1, R161.2, U36.4 (V-), U36.9 (EP)
/ch09/BVP: C98.1, R160.2, U36.7 (V+), U36.8 (~PD)
/ch09/CSP_IN: C90.2, C91.2, U33.1 (input)
/ch09/CSP_OUT: RV9.1, U33.8 (output), U34.1 (input)
/ch09/FE: C90.1, J34.1 (In), R147.2, R148.2
/ch09/N_filt: C89.1, R145.2, R146.2, R147.1, R148.1
/ch09/OUT_50: J36.1 (In), R159.2
/ch09/PZ: RV9.2, RV9.3, U34.2 (P/Z)
/ch09/SHAPER_OUT: R156.2, R162.1, U35.8 (output), U36.3 (+)
/ch09/SHVN: C95.1, R153.2, U34.4 (-Vs)
/ch09/SHVP: C94.1, R152.2, U34.5 (+Vs)
/ch09/SH_OUT: R156.1, U34.8 (output), U35.1 (input)
/ch09/TEST_IN: C91.1, J35.1 (In), R149.1
/ch10/+VS_F: C103.1, R168.2, U37.6 (+Vs)
/ch10/-VS_F: C104.1, R169.2, U37.5 (-Vs)
/ch10/BIAS_IN: J37.1 (In), R163.1, R164.1
/ch10/BLVN: C108.1, R173.2, U39.4 (-Vs)
/ch10/BLVP: C107.1, R172.2, U39.5 (+Vs)
/ch10/BUF_FB: R175.2, R176.1, U40.2 (-)
/ch10/BUF_OUT: R175.1, R177.1, R180.2, U40.6
/ch10/BVN: C110.1, R179.2, U40.4 (V-), U40.9 (EP)
/ch10/BVP: C109.1, R178.2, U40.7 (V+), U40.8 (~PD)
/ch10/CSP_IN: C101.2, C102.2, U37.1 (input)
/ch10/CSP_OUT: RV10.1, U37.8 (output), U38.1 (input)
/ch10/FE: C101.1, J38.1 (In), R165.2, R166.2
/ch10/N_filt: C100.1, R163.2, R164.2, R165.1, R166.1
/ch10/OUT_50: J40.1 (In), R177.2
/ch10/PZ: RV10.2, RV10.3, U38.2 (P/Z)
/ch10/SHAPER_OUT: R174.2, R180.1, U39.8 (output), U40.3 (+)
/ch10/SHVN: C106.1, R171.2, U38.4 (-Vs)
/ch10/SHVP: C105.1, R170.2, U38.5 (+Vs)
/ch10/SH_OUT: R174.1, U38.8 (output), U39.1 (input)
/ch10/TEST_IN: C102.1, J39.1 (In), R167.1
/ch11/+VS_F: C114.1, R186.2, U41.6 (+Vs)
/ch11/-VS_F: C115.1, R187.2, U41.5 (-Vs)
/ch11/BIAS_IN: J41.1 (In), R181.1, R182.1
/ch11/BLVN: C119.1, R191.2, U43.4 (-Vs)
/ch11/BLVP: C118.1, R190.2, U43.5 (+Vs)
/ch11/BUF_FB: R193.2, R194.1, U44.2 (-)
/ch11/BUF_OUT: R193.1, R195.1, R198.2, U44.6
/ch11/BVN: C121.1, R197.2, U44.4 (V-), U44.9 (EP)
/ch11/BVP: C120.1, R196.2, U44.7 (V+), U44.8 (~PD)
/ch11/CSP_IN: C112.2, C113.2, U41.1 (input)
/ch11/CSP_OUT: RV11.1, U41.8 (output), U42.1 (input)
/ch11/FE: C112.1, J42.1 (In), R183.2, R184.2
/ch11/N_filt: C111.1, R181.2, R182.2, R183.1, R184.1
/ch11/OUT_50: J44.1 (In), R195.2
/ch11/PZ: RV11.2, RV11.3, U42.2 (P/Z)
/ch11/SHAPER_OUT: R192.2, R198.1, U43.8 (output), U44.3 (+)
/ch11/SHVN: C117.1, R189.2, U42.4 (-Vs)
/ch11/SHVP: C116.1, R188.2, U42.5 (+Vs)
/ch11/SH_OUT: R192.1, U42.8 (output), U43.1 (input)
/ch11/TEST_IN: C113.1, J43.1 (In), R185.1
/ch12/+VS_F: C125.1, R204.2, U45.6 (+Vs)
/ch12/-VS_F: C126.1, R205.2, U45.5 (-Vs)
/ch12/BIAS_IN: J45.1 (In), R199.1, R200.1
/ch12/BLVN: C130.1, R209.2, U47.4 (-Vs)
/ch12/BLVP: C129.1, R208.2, U47.5 (+Vs)
/ch12/BUF_FB: R211.2, R212.1, U48.2 (-)
/ch12/BUF_OUT: R211.1, R213.1, R216.2, U48.6
/ch12/BVN: C132.1, R215.2, U48.4 (V-), U48.9 (EP)
/ch12/BVP: C131.1, R214.2, U48.7 (V+), U48.8 (~PD)
/ch12/CSP_IN: C123.2, C124.2, U45.1 (input)
/ch12/CSP_OUT: RV12.1, U45.8 (output), U46.1 (input)
/ch12/FE: C123.1, J46.1 (In), R201.2, R202.2
/ch12/N_filt: C122.1, R199.2, R200.2, R201.1, R202.1
/ch12/OUT_50: J48.1 (In), R213.2
/ch12/PZ: RV12.2, RV12.3, U46.2 (P/Z)
/ch12/SHAPER_OUT: R210.2, R216.1, U47.8 (output), U48.3 (+)
/ch12/SHVN: C128.1, R207.2, U46.4 (-Vs)
/ch12/SHVP: C127.1, R206.2, U46.5 (+Vs)
/ch12/SH_OUT: R210.1, U46.8 (output), U47.1 (input)
/ch12/TEST_IN: C124.1, J47.1 (In), R203.1
GND: C12.2, C15.2, C16.2, C17.2, C18.2, C19.2, C20.2, C21.2, C22.2, C23.2, C26.2, C27.2, C28.2, C29.2, C30.2, C31.2, C32.2, C33.2, C34.2, C37.2, C38.2, C39.2, C40.2, C41.2, C42.2, C43.2, C44.2, C45.2, C48.2, C49.2, C50.2, C51.2, C52.2, C53.2, C54.2, C55.2, C56.2, C59.2, C60.2, C61.2, C62.2, C63.2, C64.2, C65.2, C66.2, C67.2, C70.2, C71.2, C72.2, C73.2, C74.2, C75.2, C76.2, C77.2, C78.2, C81.2, C82.2, C83.2, C84.2, C85.2, C86.2, C87.2, C88.2, C89.2, C92.2, C93.2, C94.2, C95.2, C96.2, C97.2, C98.2, C99.2, C100.2, C103.2, C104.2, C105.2, C106.2, C107.2, C108.2, C109.2, C110.2, C111.2, C114.2, C115.2, C116.2, C117.2, C118.2, C119.2, C120.2, C121.2, C122.2, C125.2, C126.2, C127.2, C128.2, C129.2, C130.2, C131.2, C132.2, J5.2 (Ext), J6.2 (Ext), J7.2 (Ext), J8.2 (Ext), J9.2 (Ext), J10.2 (Ext), J11.2 (Ext), J12.2 (Ext), J13.2 (Ext), J14.2 (Ext), J15.2 (Ext), J16.2 (Ext), J17.2 (Ext), J18.2 (Ext), J19.2 (Ext), J20.2 (Ext), J21.2 (Ext), J22.2 (Ext), J23.2 (Ext), J24.2 (Ext), J25.2 (Ext), J26.2 (Ext), J27.2 (Ext), J28.2 (Ext), J29.2 (Ext), J30.2 (Ext), J31.2 (Ext), J32.2 (Ext), J33.2 (Ext), J34.2 (Ext), J35.2 (Ext), J36.2 (Ext), J37.2 (Ext), J38.2 (Ext), J39.2 (Ext), J40.2 (Ext), J41.2 (Ext), J42.2 (Ext), J43.2 (Ext), J44.2 (Ext), J45.2 (Ext), J46.2 (Ext), J47.2 (Ext), J48.2 (Ext), R23.2, R32.2, R41.2, R50.2, R59.2, R68.2, R77.2, R86.2, R95.2, R104.2, R113.2, R122.2, R131.2, R140.2, R149.2, R158.2, R167.2, R176.2, R185.2, R194.2, R203.2, R212.2, U5.2 (GND), U5.4 (GND), U5.7 (GND), U6.3 (GND), U6.6 (GND), U6.7 (GND), U7.2 (GND), U7.3 (GND), U7.6 (GND), U7.7 (GND), U8.1 (REF), U9.2 (GND), U9.4 (GND), U9.7 (GND), U10.3 (GND), U10.6 (GND), U10.7 (GND), U11.2 (GND), U11.3 (GND), U11.6 (GND), U11.7 (GND), U12.1 (REF), U13.2 (GND), U13.4 (GND), U13.7 (GND), U14.3 (GND), U14.6 (GND), U14.7 (GND), U15.2 (GND), U15.3 (GND), U15.6 (GND), U15.7 (GND), U16.1 (REF), U17.2 (GND), U17.4 (GND), U17.7 (GND), U18.3 (GND), U18.6 (GND), U18.7 (GND), U19.2 (GND), U19.3 (GND), U19.6 (GND), U19.7 (GND), U20.1 (REF), U21.2 (GND), U21.4 (GND), U21.7 (GND), U22.3 (GND), U22.6 (GND), U22.7 (GND), U23.2 (GND), U23.3 (GND), U23.6 (GND), U23.7 (GND), U24.1 (REF), U25.2 (GND), U25.4 (GND), U25.7 (GND), U26.3 (GND), U26.6 (GND), U26.7 (GND), U27.2 (GND), U27.3 (GND), U27.6 (GND), U27.7 (GND), U28.1 (REF), U29.2 (GND), U29.4 (GND), U29.7 (GND), U30.3 (GND), U30.6 (GND), U30.7 (GND), U31.2 (GND), U31.3 (GND), U31.6 (GND), U31.7 (GND), U32.1 (REF), U33.2 (GND), U33.4 (GND)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; also elsewhere on the board

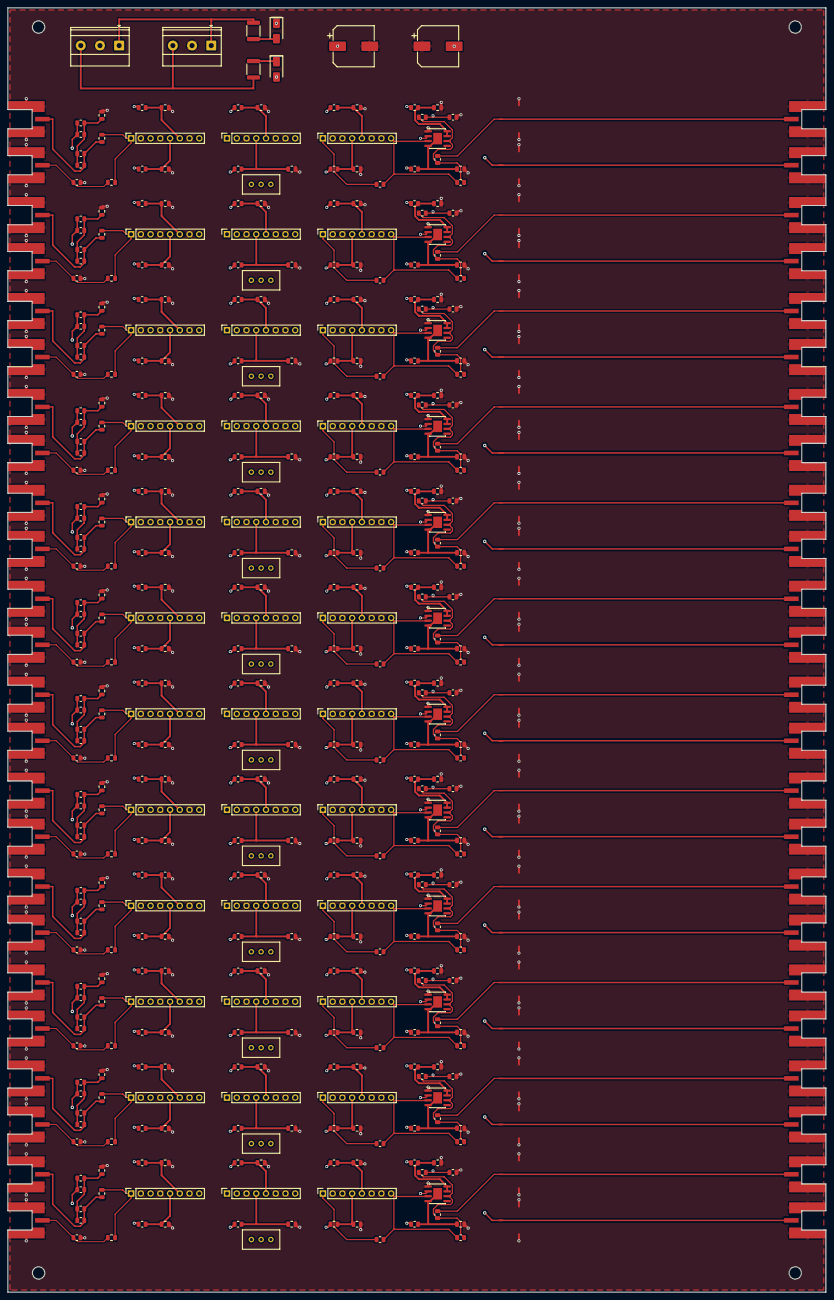
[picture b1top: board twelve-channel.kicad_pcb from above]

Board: 4 copper layers, 213.2 x 334.7 mm, 468 parts (0 on the bottom side), 247 nets.

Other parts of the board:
H1, H2, H3, H4: MountingHole_3.2mm_M3

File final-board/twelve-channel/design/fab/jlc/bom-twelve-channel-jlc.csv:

Comment,Designator,Footprint,JLCPCB Part #
49.9R 1% 0805,"R15,R33,R51,R69,R87,R105,R123,R141,R159,R177,R195,R213",0805,C17720
0.22uF 100V X7R 0805,"C2,C13,C24,C35,C46,C57,C68,C79,C90,C101,C112,C123",0805,C2167405
0R jumper 0805,"R18,R36,R54,R72,R90,R108,R126,R144,R162,R180,R198,R216",0805,C17477
100nF 100V X7R 0805,"C1,C12,C23,C34,C45,C56,C67,C78,C89,C100,C111,C122",0805,C28233
10k 1% 0805,"R1,R3,R19,R21,R37,R39,R55,R57,R73,R75,R91,R93,R109,R111,R127,R129,R145,R147,R163,R165,R181,R183,R199,R201",0805,C84376
10uF 25V X5R 0805,"C4,C5,C6,C7,C8,C9,C15,C16,C17,C18,C19,C20,C26,C27,C28,C29,C30,C31,C37,C38,C39,C40,C41,C42,C48,C49,C50,C51,C52,C53,C59,C60,C61,C62,C63,C64,C70,C71,C72,C73,C74,C75,C81,C82,C83,C84,C85,C86,C92,C93,C94,C95,C96,C97,C103,C104,C105,C106,C107,C108,C114,C115,C116,C117,C118,C119,C125,C126,C127,C128,C129,C130",0805,C15850
10pF 1% 50V C0G 0805,"C3,C14,C25,C36,C47,C58,C69,C80,C91,C102,C113,C124",0805,C541512
4.7R 0805,"R6,R7,R8,R9,R10,R11,R24,R25,R26,R27,R28,R29,R42,R43,R44,R45,R46,R47,R60,R61,R62,R63,R64,R65,R78,R79,R80,R81,R82,R83,R96,R97,R98,R99,R100,R101,R114,R115,R116,R117,R118,R119,R132,R133,R134,R135,R136,R137,R150,R151,R152,R153,R154,R155,R168,R169,R170,R171,R172,R173,R186,R187,R188,R189,R190,R191,R204,R205,R206,R207,R208,R209",0805,C2933459
47R 0805,"R5,R23,R41,R59,R77,R95,R113,R131,R149,R167,R185,R203",0805,C17714
470uF 35V SMD 10x10.5,"C133,C134",SMD-10x10.5,C494847
PTC 1.1A 24V 1812,"F1,F2",1812,C207066
Schottky 40V 3A SMA,"D1,D2",SMA,C8678
MCX edge jack 50R (BWMCX-KEF),"J1,J2,J3,J4,J5,J6,J7,J8,J9,J10,J11,J12,J13,J14,J15,J16,J17,J18,J19,J20,J21,J22,J23,J24,J25,J26,J27,J28,J29,J30,J31,J32,J33,J34,J35,J36,J37,J38,J39,J40,J41,J42,J43,J44,J45,J46,J47,J48",MCX-SMD,C5250059
200k trimpot 3296W 3-pin THT,"RV1,RV2,RV3,RV4,RV5,RV6,RV7,RV8,RV9,RV10,RV11,RV12",Potentiometer-3296W-3P,C48997932
Screw terminal 3-pos 5.0mm horiz (KF128),"J49,J50",TerminalBlock-P5.0mm-3P,C474951
